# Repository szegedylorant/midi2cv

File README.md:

# MIDI Interface

MIDI to Clock, CV and Gate interface in 4 hp wide Eurorack format based on the Arduino Nano v3.

 "3d rendered image of the two boards"

## Functions

* 4hp wide
* TRS MIDI Type A
* Hardware MIDI Thru
* MIDI clock to 16th note clock signal
* MIDI clock to DIN SYNC 24ppqn signal
* MIDI CC using 7 bit PWM Output
* 1V / Octave Pitch CV using 7 bit PWM Output
* Note glide knob
* Note on gate output

## Sources

### Code based on:
* - https://github.com/dhaillant/midi8d
* - https://github.com/kassu/KassutronicsQuantizer
 
### Hardware based on:
* - https://n-audio.net/designing-midi-in-and-midi-out-schematics/
* - https://github.com/dhaillant/midi8d
* - https://github.com/kassu/kassutronics/tree/master/documentation/Quantizer

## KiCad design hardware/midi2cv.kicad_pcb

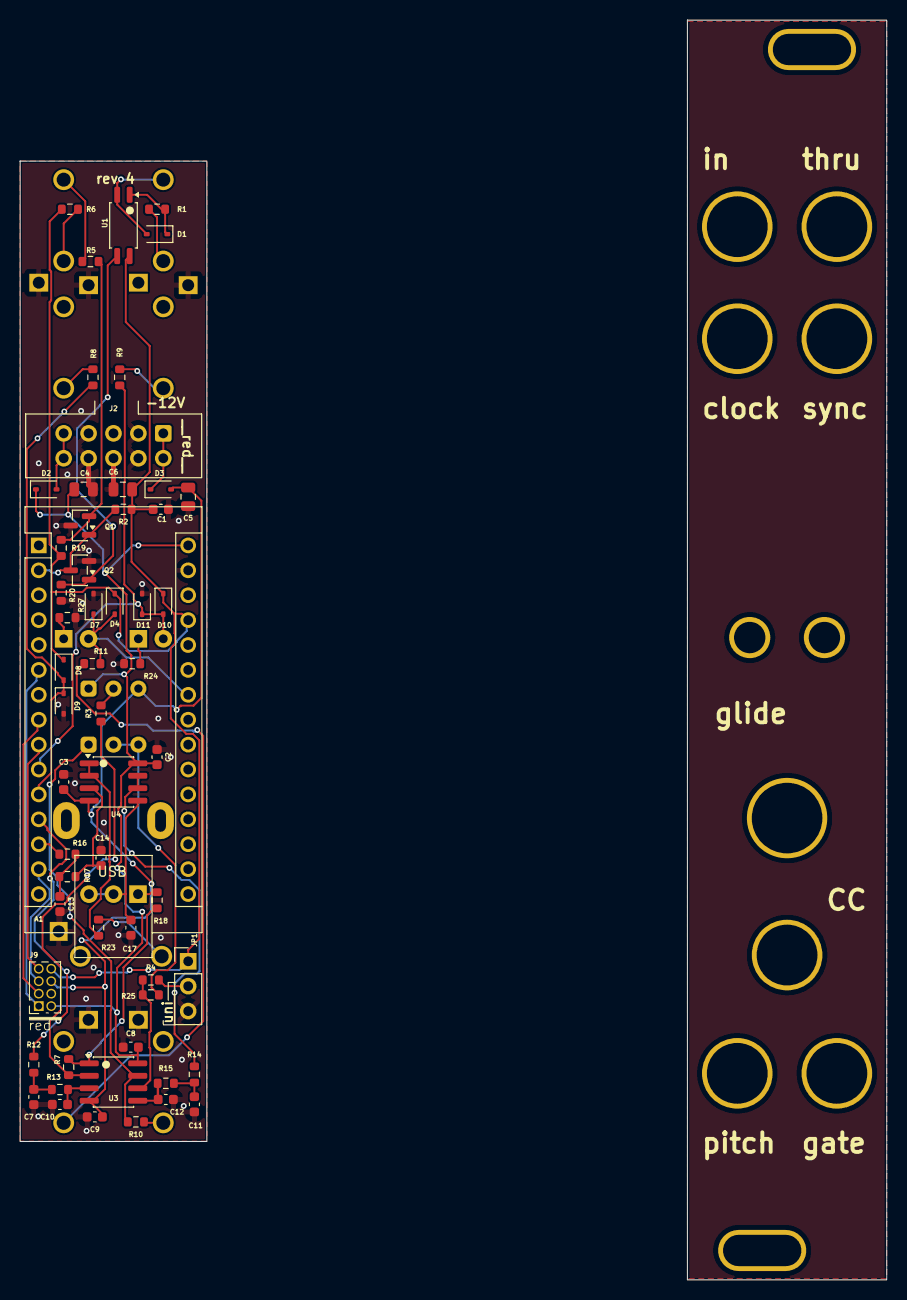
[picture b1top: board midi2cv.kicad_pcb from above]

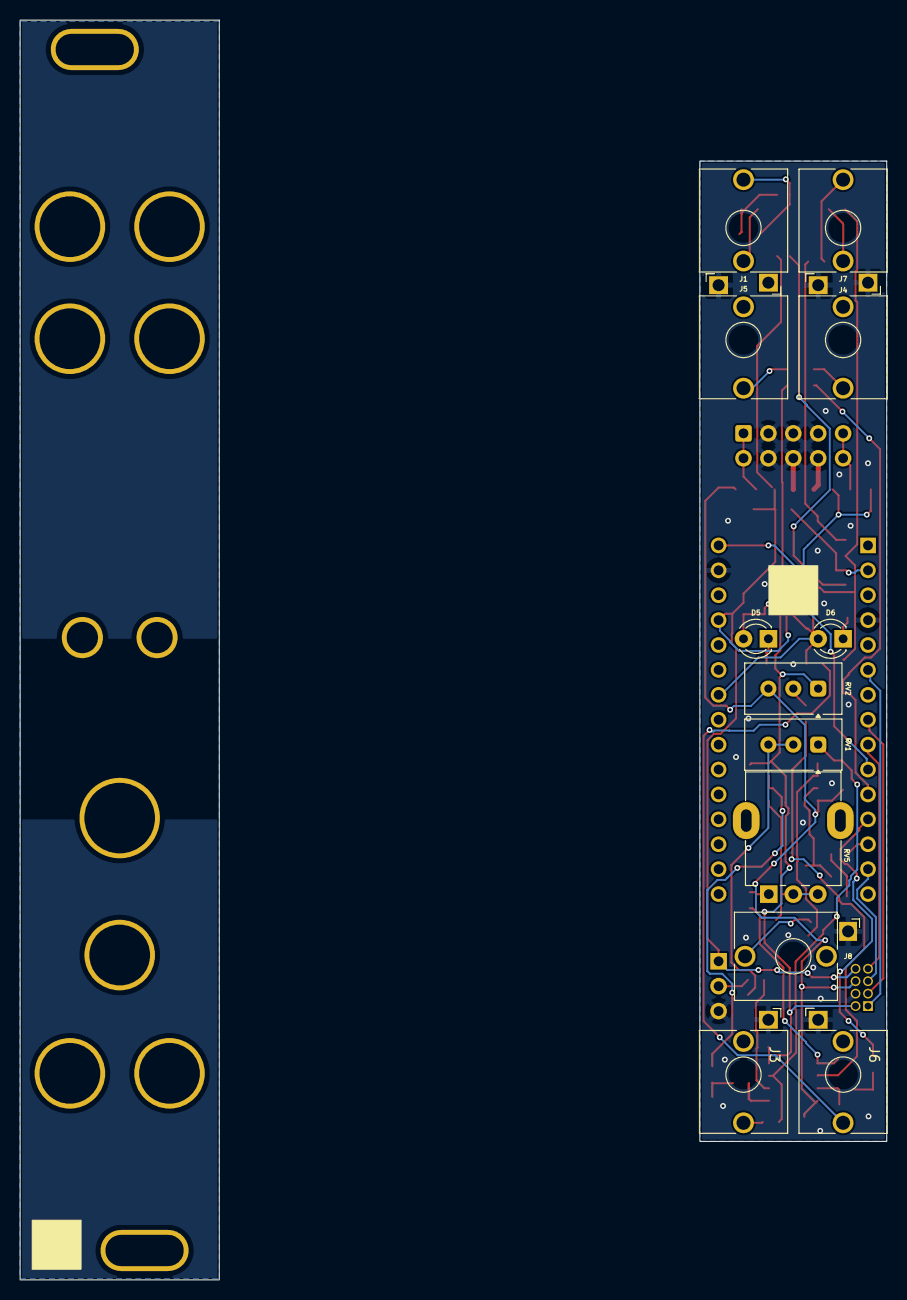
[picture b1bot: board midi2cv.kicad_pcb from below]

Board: 2 copper layers, 19.1 x 100.0 mm, 83 parts (12 on the bottom side), 47 nets.

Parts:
A1: Arduino_Nano_v3.x; Arduino_Nano
B: Board
B2: Board; Board_4hp_100mm
B3: Front_Plate; Front_Plate_4hp_cut
C1, C2, C3, C8, C9: 100n; C_0603_1608Metric
C4, C5, C6: 10u; C_0805_2012Metric
C7, C10, C11, C12, C13, C14: 1n; C_0603_1608Metric
C17: 470n; C_0603_1608Metric
D1: 1N4148WS; D_SOD-323
D2, D3, D4, D7, D8, D9, D10, D11: 1N5819WS; D_SOD-323
D5, D6: LED; LED_D3.0mm
F: Board
H1, H2, H3, H4, H5, H6, H7: 6mm; DrillHole_D6.00
H8, H9: 3mm; DrillHole_D3.00
H10: 7mm; DrillHole_D7.00
J1: MIDI In; Jack_3.5mm_QingPu_WQP-PJ366ST_Vertical_CircularHoles_L
J2: EuroPower10_THT; IDC-Header_2x05_P2.54mm_Vertical_PinOnly
J3: Pitch; Jack_3.5mm_QingPu_WQP-PJ398SM_Vertical_CircularHoles_R
J4: Clock; Jack_3.5mm_QingPu_WQP-PJ398SM_Vertical_CircularHoles_L
J5: Clock2; Jack_3.5mm_QingPu_WQP-PJ398SM_Vertical_CircularHoles_L
J6: Gate; Jack_3.5mm_QingPu_WQP-PJ398SM_Vertical_CircularHoles_L
J7: MIDI Through; Jack_3.5mm_QingPu_WQP-PJ366ST_Vertical_CircularHoles_L
J8: CC; Jack_3.5mm_QingPu_WQP-PJ398SM_Vertical_CircularHoles_L
J9: Conn_02x04_Odd_Even; PinSocket_2x04_P1.27mm_Vertical
JP1: Jumper_3_Bridged12; PinHeader_1x03_P2.54mm_Vertical
Q1: MMBT5401; SOT-23
Q2: MMBT5551L; SOT-23
R1, R5, R6: 220R; R_0603_1608Metric
R2, R7, R8, R9, R10, R11, R19, R20, R23: 1k; R_0603_1608Metric
R3: 1M; R_0603_1608Metric
R4, R25: 100k; R_0603_1608Metric
R12, R13, R14, R15, R16, R17: 15k; R_0603_1608Metric
R18: 100; R_0603_1608Metric
R24, R27: 4k7; R_0603_1608Metric
RV1: 20k; Potentiometer_Vishay_T93XA_Horizontal
RV2: 100k; Potentiometer_Vishay_T93XA_Horizontal
RV5: A100k; Potentiometer_Alpha_RD901F-40-00D_Single_Vertical
U1: EL3H7(C)(TA)-G; SSOP-4_4.4x2.6mm_P1.27mm
U3, U4: TL072; SOIC-8_3.9x4.9mm_P1.27mm

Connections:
+12V: D2.2 (A), J2.9 (+12V), J2.10 (+12V)
-12V: D3.1 (K), J2.1 (-12V), J2.2 (-12V)
B_+5V: A1.27 (+5V), C1.1, C6.1, D4.1 (K), D8.1 (K), D10.1 (K), J9.8, JP1.1 (A), R2.2, R6.1, R19.2, U1.4
B_+12V: A1.30 (VIN), C2.1, C4.1, C8.1, D2.1 (K), J9.2, RV2.1, U3.8 (V+), U4.8 (V+)
B_-12V: C3.2, C5.2, C9.2, D3.2 (A), J9.6, RV2.3, U3.4 (V-), U4.4 (V-)
B_GND: A1.4 (GND), A1.29 (GND), C1.2, C2.2, C3.1, C4.2, C5.1, C6.2, C7.2, C8.2, C9.1, C10.2, C11.2, C12.2, C13.2, C14.2, C17.2, D7.2 (A), D9.2 (A), D11.2 (A), J2.3 (GND), J2.4 (GND), J2.5 (GND), J2.6 (GND), J2.7 (GND), J2.8 (GND), J3.S, J4.S, J5.S, J6.S, J7.S, J8.S, J9.4, JP1.3 (B), Q1.3 (C), Q2.2 (E), R20.1, R24.2, R27.2
CC: A1.13 (D10), R16.2
CLOCK: A1.11 (D8), D8.2 (A), D9.1 (K), R8.2
CLOCK2: A1.10 (D7), D5.2 (A), D10.2 (A), D11.1 (K), R9.2
EXP1: A1.6 (D3), J9.1
EXP3: A1.8 (D5), J9.3
EXP5: A1.14 (D11), J9.5
EXP7: A1.9 (D6), J9.7
GATE: A1.24 (A5), D4.2 (A), D6.2 (A), D7.1 (K), R11.2
MIDI_IN: A1.2 (D0/RX), Q1.1 (B), Q2.3 (C), R2.1
unnamed: C7.1, R12.1, R13.2
unnamed: C11.1, R14.1, R15.2
unnamed: C13.1, R16.1, R17.2
unnamed: D1.2 (A), J1.T, U1.2
unnamed: D1.1 (K), R1.2, U1.1
unnamed: D5.1 (K), R24.1
unnamed: D6.1 (K), R27.1
unnamed: J1.R, R1.1
unnamed: J3.T, R10.1
unnamed: J4.T, R8.1
unnamed: J5.T, R9.1
unnamed: J6.T, R11.1
unnamed: J7.R, R6.2
unnamed: J7.T, R5.2
unnamed: J8.T, R23.1
unnamed: JP1.2 (C), R4.2
unnamed: Q1.2 (E), R5.1, R19.1
unnamed: Q2.1 (B), R20.2, U1.3
unnamed: R3.2, RV2.2
unnamed: R10.2, RV1.1, U3.7
unnamed: R18.1, RV5.1
unnamed: R25.1, RV1.2, RV1.3
unnamed: C10.1, R13.1, U3.3 (+)
unnamed: R3.1, R7.2, U3.2 (-)
unnamed: C12.1, R15.1, U3.5 (+)
unnamed: R4.1, R25.2, U3.6 (-)
unnamed: C14.1, R17.1, U4.3 (+)
unnamed: R23.2, U4.1, U4.2 (-)
unnamed: C17.1, RV5.2, RV5.3, U4.5 (+)
PITCH: A1.12 (D9), R12.2
SLEW_IN: R7.1, R18.2, U3.1
SLEW_OUT: R14.2, U4.6 (-), U4.7

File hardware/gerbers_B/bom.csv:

Comment,Designator,Footprint,LCSC
4k7,"R24,R27",Resistor_SMD:R_0603_1608Metric,C23162
1N5819WS,"D2,D3,D4,D7,D8,D9,D10,D11",Diode_SMD:D_SOD-323,C191023
1k,"R2,R7,R8,R9,R10,R11,R19,R20,R23",Resistor_SMD:R_0603_1608Metric,C21190
10u,"C4,C5,C6",Capacitor_SMD:C_0805_2012Metric,C15850
100n,"C1,C2,C3,C8,C9",Capacitor_SMD:C_0603_1608Metric,C14663
TL072,"U3,U4",Package_SO:SOIC-8_3.9x4.9mm_P1.27mm,C6961
10n,C17,Capacitor_SMD:C_0603_1608Metric,C57112
15k,"R12,R13,R14,R15,R16,R17",Resistor_SMD:R_0603_1608Metric,C22809
1n,"C7,C10,C11,C12,C13,C14",Capacitor_SMD:C_0603_1608Metric,C1588
100k,"R4,R25",Resistor_SMD:R_0603_1608Metric,C25803
100,R18,Resistor_SMD:R_0603_1608Metric,C22775
1M,R3,Resistor_SMD:R_0603_1608Metric,C22935
220R,"R1,R5,R6",Resistor_SMD:R_0603_1608Metric,C22962
MMBT5551L,"Q1,Q2",Package_TO_SOT_SMD:SOT-23,C2145
1N4148WS,D1,Diode_SMD:D_SOD-323,C2128
EL3H7(C)(TA)-G,U1,Package_SO:SSOP-4_4.4x2.6mm_P1.27mm,C92243

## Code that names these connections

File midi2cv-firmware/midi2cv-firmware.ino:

/*
 * MIDI Interface
 *
 * MIDI clock to 16th note clock signal
 * MIDI clock to DYN SYNC 24ppqn signal
 *
 * Code based on:
 * - https://github.com/dhaillant/midi8d
 * - https://github.com/kassu/KassutronicsQuantizer
 *
 * Hardware based on:
 * - https://n-audio.net/designing-midi-in-and-midi-out-schematics/
 * - https://electricdruid.net/product/midi-inoutthru-pcb/
 * - https://github.com/dhaillant/midi8d
 * - https://github.com/kassu/kassutronics/tree/master/documentation/Quantizer
 * 
*/
// #define PITCH_CALIBRATION 5000  // uncomment for calibration mode

// Macros to set and clear a single bit in any register
#ifndef cbi
#define cbi(sfr, bit) (_SFR_BYTE(sfr) &= ~_BV(bit))
#endif
#ifndef sbi
#define sbi(sfr, bit) (_SFR_BYTE(sfr) |= _BV(bit))
#endif

#define TRIGGER_LENGTH 1000  // clock and sync gate length in microseconds

#include <Arduino.h>
#include <MIDI.h>  // https://github.com/FortySevenEffects/arduino_midi_library.git

const uint8_t PIN_CLOCK = 8;
const uint8_t PIN_CLOCK2 = 7;

const uint8_t PIN_CC = 10;    // PWM pin
const uint8_t PIN_PITCH = 9;  // PWM pin
const uint8_t PIN_GATE = A5;

const uint8_t PIN_SERIAL_RX = 0;
const uint8_t PIN_SERIAL_TX = 1;


// currently unused pins for extension board
const uint8_t PIN_EXP1 = 3;
const uint8_t PIN_EXP3 = 5;
const uint8_t PIN_EXP5 = 11;
const uint8_t PIN_EXP7 = 6;

const uint8_t MIDI_CHANNEL = MIDI_CHANNEL_OMNI;  // Set midi channel here
const uint8_t CC_NUMBER = 27;                    // TODO: find a good default...


MIDI_CREATE_DEFAULT_INSTANCE();

bool isRunning = false;

class Trigger {
public:
  uint8_t step = 0;
  bool isTriggered = false;

  Trigger(const uint8_t pin)
    : PIN(pin) {}

  void update() {
    long now = micros();
    if (isTriggered) {  // pick up trigger signal
      triggerStart = now;
      isTriggered = false;
    }
    if (now - triggerStart < TRIGGER_LENGTH) {  // keep pin high for the predefined duration
      digitalWrite(PIN, HIGH);
    } else {
      digitalWrite(PIN, LOW);
    }
  }
private:
  const uint8_t PIN;
  long triggerStart = 0;
};

Trigger clock(PIN_CLOCK2);
Trigger sync(PIN_CLOCK);

void startupBlinkLED() {
  digitalWrite(PIN_GATE, LOW);
  digitalWrite(PIN_CLOCK2, LOW);
  delay(1000);
  digitalWrite(PIN_GATE, HIGH);
  delay(200);
  digitalWrite(PIN_GATE, LOW);
  digitalWrite(PIN_CLOCK2, HIGH);
  delay(200);
  digitalWrite(PIN_CLOCK2, LOW);
}
void setup() {
  // Serial.begin(115200);
  // Serial.begin(31250);

  setupPWM();

  pinMode(PIN_GATE, OUTPUT);
  pinMode(PIN_CLOCK, OUTPUT);
  pinMode(PIN_CLOCK2, OUTPUT);
  digitalWrite(PIN_GATE, HIGH);
  digitalWrite(PIN_CLOCK, HIGH);
  digitalWrite(PIN_CLOCK2, HIGH);

#ifndef PITCH_CALIBRATION
  MIDI.setHandleClock(handleClock);        // called on each clock pulse
  MIDI.setHandleStart(handleStart);        // called on START message
  MIDI.setHandleContinue(handleContinue);  // called on CONTINUE message
  MIDI.setHandleStop(handleStop);          // called on STOP message
  MIDI.setHandleNoteOn(handleNoteOn);
  MIDI.setHandleNoteOff(handleNoteOff);
  MIDI.setHandleControlChange(handleCC);

  MIDI.begin(MIDI_CHANNEL);  // filter MIDI channel
#endif

  delay(1000);
  // Serial.println("Serial ready...");
  startupBlinkLED();
}

void loop() {

#if defined(PITCH_CALIBRATION)
  writePitch(12);  // for unipolar output: 1V
  delay(PITCH_CALIBRATION);
  writePitch(60);  // for unipolar output: 5V
  delay(PITCH_CALIBRATION);
  writePitch(108);  // for unipolar output: 9V
  delay(PITCH_CALIBRATION);
#else
  MIDI.read();
  clock.update();
  sync.update();
#endif
}

void handleStart() {
  // Serial.println("Start");

  isRunning = true;
  sync.step = 0;
  clock.step = 0;
}

void handleContinue() {
  // Serial.println("Continue");

  isRunning = true;
}

void handleStop() {
  // Serial.println("Stop");

  isRunning = false;
}

void handleClock() {
  // Serial.println("Tick");
  if (isRunning) {
    clock.isTriggered = (clock.step == 0);
    sync.isTriggered = true;

    sync.step++;
    sync.step = sync.step % 96;  // 24ppqn MIDI clock, directly suitable for DIN SYNC; fold at each bar to avoid overflow
    clock.step = sync.step % 6;  // 16th notes; as a division of the midi clock
  }
}

void handleNoteOn(midi::Channel channel, byte note, byte velocity) {
  // convert note V/Oct
  // one step in the PWM output is one note, so only shift could be adjusted
  // Pitch output needs hardware calibration
  // C-2 is midi note 0
  // C 3 is midi note 60
  // C 8 is midi note 120
  uint8_t noteIndex = note;
  writePitch(noteIndex);

  // gate on unless velocity is 0
  if (velocity == 0) {
    digitalWrite(PIN_GATE, LOW);
  } else {
    digitalWrite(PIN_GATE, HIGH);
  }
}

void handleNoteOff(midi::Channel channel, byte note, byte velocity) {
  // keep last pitch aka do nothing
  // gate off
  digitalWrite(PIN_GATE, LOW);
}

void handleCC(midi::Channel channel, byte cc_number, byte value) {
  if (cc_number == CC_NUMBER) {  // filter CC number
    writeCC(value);
  }
}

// This is taken from https://github.com/kassu/KassutronicsQuantizer/blob/master/KassutronicsQuantizer/Hardware.ino
void setupPWM() {
  // Setup timer1 for PWM on pin 9 and 10

  // The pins should be outputs
  pinMode(PIN_PITCH, OUTPUT);
  // pinMode(9, OUTPUT);
  pinMode(PIN_CC, OUTPUT);
  // pinMode(10, OUTPUT);

  // --- Clock prescaler ---
  // The PWM clock runs at the CPU rate (16 MHz) divided by a prescaler.
  // For settings 0x01 -- 0x05, the prescaler is 1, 8, 64, 256, 1024, respectively.
  // We use the fastest option:
  TCCR1B = TCCR1B & 0b11111000 | 0x01;

  // --- Waveform Generation Mode (WGM)
  /* WGM13:0 sets the PWM mode. Of the 16 modes, these are most interesting:
     5 - 7: Fast PWM 8-10 bit, respectively
     14: Fast PWM, frequency set by ICR1 register
     15: Fast PWM, frequency set by OCR1A register
 
     In mode 14 and 15, the PWM frequency can be chosen very flexibly: 
  
         fPWM = fCPU / (N * (TOP+1))
  
     where fIO is the CPU clock, N is the prescaler set above and TOP is the value in
     either ICR1 or OCR1A (mode 14 or 15, resp.).
     
     We use mode 14, because then we can freely choose the frequency, but have the OCR1A register
     available to control the PWM on pin 9.
    */
  // The mode setting is spread over the two timer registers,so we set it one bit at the time (14 = 0b1110 = set set set clear)
  sbi(TCCR1B, WGM13);
  sbi(TCCR1B, WGM12);
  sbi(TCCR1A, WGM11);
  cbi(TCCR1A, WGM10);

  // Set ICR1 register define frequency (see formula above) and resolution (valid output values are 0 to ICR1)
  //ICR1 = 0x01FF; // 9 bit
  ICR1 = 0x007F;  // 7 bit

  // Compare Output Mode - COM1A1, COM1A0, COM1B1, COM1B0 (first 4 bits of TCCR1A, respectively)
  // These set the mode for output A (=pin 9) and output B (=pin 10), respectively. In fast PWM mode, the modes are:
  //   0b00 - Normal port (disable PWM)
  //   0b01 - Only in WGM mode 14 or 15 (see above): Toggle output A on Compare Match. Output B is normal port (PWM disabled)
  //          I'm not sure what the point of this is. It seems you get always 50% duty cycle and half the normal fast PWM frequency,
  //          but then you can set the phase with register OCR1A (or analogWrite(9,phase) )
  //   0b10 - non-inverting PWM
  //   0b11 - inverting PWM
  // Arduinos analogWrite sets the first bit for the respective port each time you call analogWrite (so you can switch to
  // digitalWrite and back whenever you feel like it). Let's set them all explicitly in the beginning, so we can write the
  // registers directly.
  sbi(TCCR1A, COM1A1);
  cbi(TCCR1A, COM1A0);
  sbi(TCCR1A, COM1B1);
  cbi(TCCR1A, COM1B0);

  // Write 0 to both ports as initial value
  OCR1A = 0;
  OCR1B = 0;
}

inline void writePitch(uint8_t pitch) {
  OCR1A = pitch - 1; // TODO: fix offset adjustment range in hardware
}

inline void writeCC(uint8_t cc) {
  OCR1B = cc;
}

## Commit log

2025-11-20 first schematics sketch
2025-11-20 add stereo jack footprint
2026-01-03 routed pcb
2026-01-03 update routing
2026-01-04 add gerbers and bom
2026-02-02 add rev 2 and rev 3, now with correct trs midi A
2026-02-02 update firmware with calibration
2026-02-05 add 3d rendered image
2026-02-05 reorganize folders
2026-03-01 main board rev 4: fix midi thru, led arrangement, glide cap value. fix sync trigger output
2026-03-16 update calibration
